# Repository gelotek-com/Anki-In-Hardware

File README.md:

# Physical Anki Device

Building a physical flashcard device inspired by **Anki** and **spaced repetition**.

## YouTube Series
Watch the full project here:  
🎥 https://www.youtube.com/playlist?list=PLZI8gkIZC2W3yhb4EUrMZ4vrkucjjzuon
## My website
My website for more details:
https://gelotek.com/AIH/

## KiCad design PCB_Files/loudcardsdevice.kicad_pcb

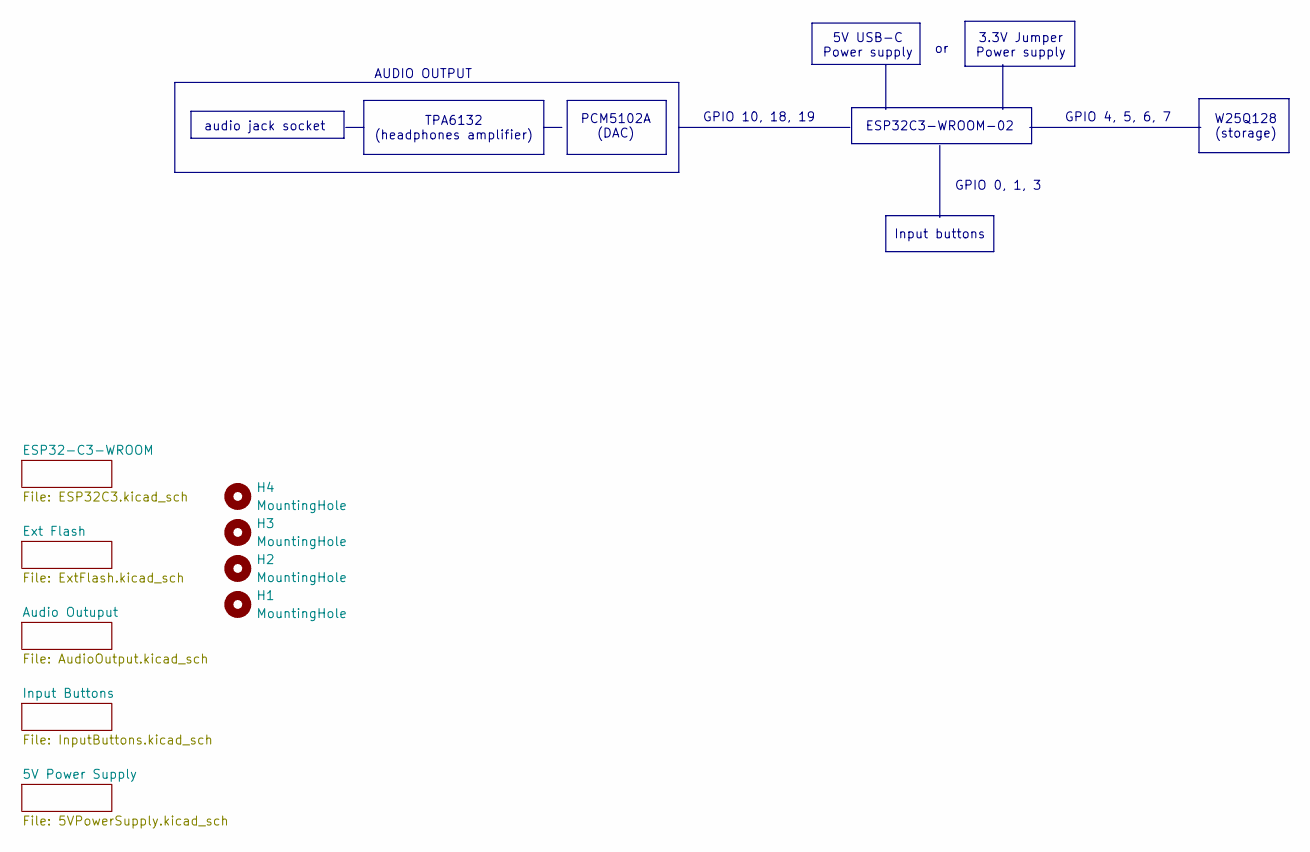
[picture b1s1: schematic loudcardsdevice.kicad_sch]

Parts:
H1, H2, H3, H4: MountingHole; MountingHole_2.1mm

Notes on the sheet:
ESP32C3-WROOM-02
GPIO 10, 18, 19
PCM5102A (DAC)
3.3V Jumper Power supply
GPIO 0, 1, 3
5V USB-C Power supply
AUDIO OUTPUT
TPA6132 (headphones amplifier)
Input buttons
W25Q128 (storage)
GPIO 4, 5, 6, 7
audio jack socket

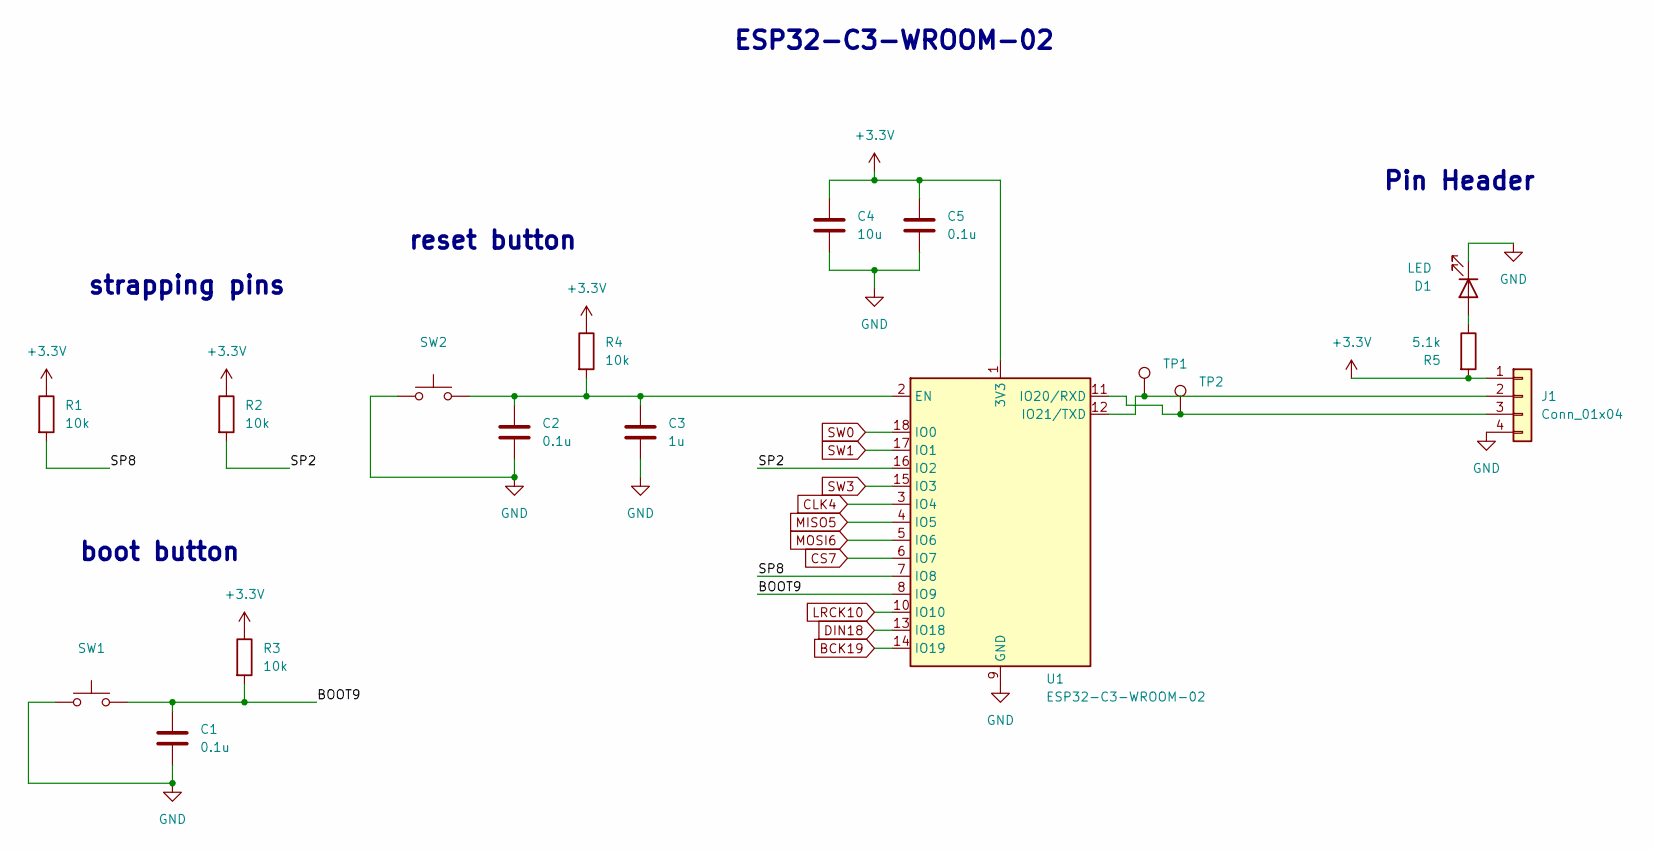
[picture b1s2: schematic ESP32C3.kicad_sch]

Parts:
C1, C2, C5: 0.1u; C_0603_1608Metric; MPN 0603B104K250CT
C3: 1u; C_0603_1608Metric; MPN CL10A105KO8NNNC
C4: 10u; C_0603_1608Metric; MPN CL10A106MQ8NNNC
D1: LED; LED_0603_1608Metric; MPN YLED0603R
J1: Conn_01x04; PinHeader_1x04_P2.54mm_Vertical; MPN PZ254V-11-04P
R1, R2, R3, R4: 10k; R_0603_1608Metric; MPN RC0603FR-0710KL
R5: 5.1k; R_0603_1608Metric; MPN FRC0603F5101TS
SW1, SW2: SW_Push; SW_PUSH_6mm; MPN TS665CJ
TP1, TP2: TestPoint; TestPoint_Pad_1.0x1.0mm
U1: ESP32-C3-WROOM-02; MPN ESP32-C3-WROOM-02-H4

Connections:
+3.3V: C4.1, C5.1, J1.1, R1.1, R2.1, R3.1, R4.1, R5.2, U1.1 (3V3); also elsewhere on the board
/ESP32-C3-WROOM/BOOT9: C1.1, R3.2, SW1.2, U1.8 (IO9)
/ESP32-C3-WROOM/SP2: R2.2, U1.16 (IO2)
/ESP32-C3-WROOM/SP8: R1.2, U1.7 (IO8)
BCK19: U1.14 (IO19); also elsewhere on the board
CLK4: U1.3 (IO4); also elsewhere on the board
CS7: U1.6 (IO7); also elsewhere on the board
DIN18: U1.13 (IO18); also elsewhere on the board
GND: C1.2, C2.2, C3.2, C4.2, C5.2, D1.1 (K), J1.4, SW1.1, SW2.1, U1.9 (GND), U1.19 (GND); also elsewhere on the board
LRCK10: U1.10 (IO10); also elsewhere on the board
MISO5: U1.4 (IO5); also elsewhere on the board
MOSI6: U1.5 (IO6); also elsewhere on the board
unnamed: D1.2 (A), R5.1
unnamed: J1.2, TP1.1, U1.12 (IO21/TXD)
unnamed: J1.3, TP2.1, U1.11 (IO20/RXD)
unnamed: C2.1, C3.1, R4.2, SW2.2, U1.2 (EN)
SW0: U1.18 (IO0); also elsewhere on the board
SW1: U1.17 (IO1); also elsewhere on the board
SW3: U1.15 (IO3); also elsewhere on the board

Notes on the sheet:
strapping pins
boot button
Pin Header
reset button
ESP32-C3-WROOM-02

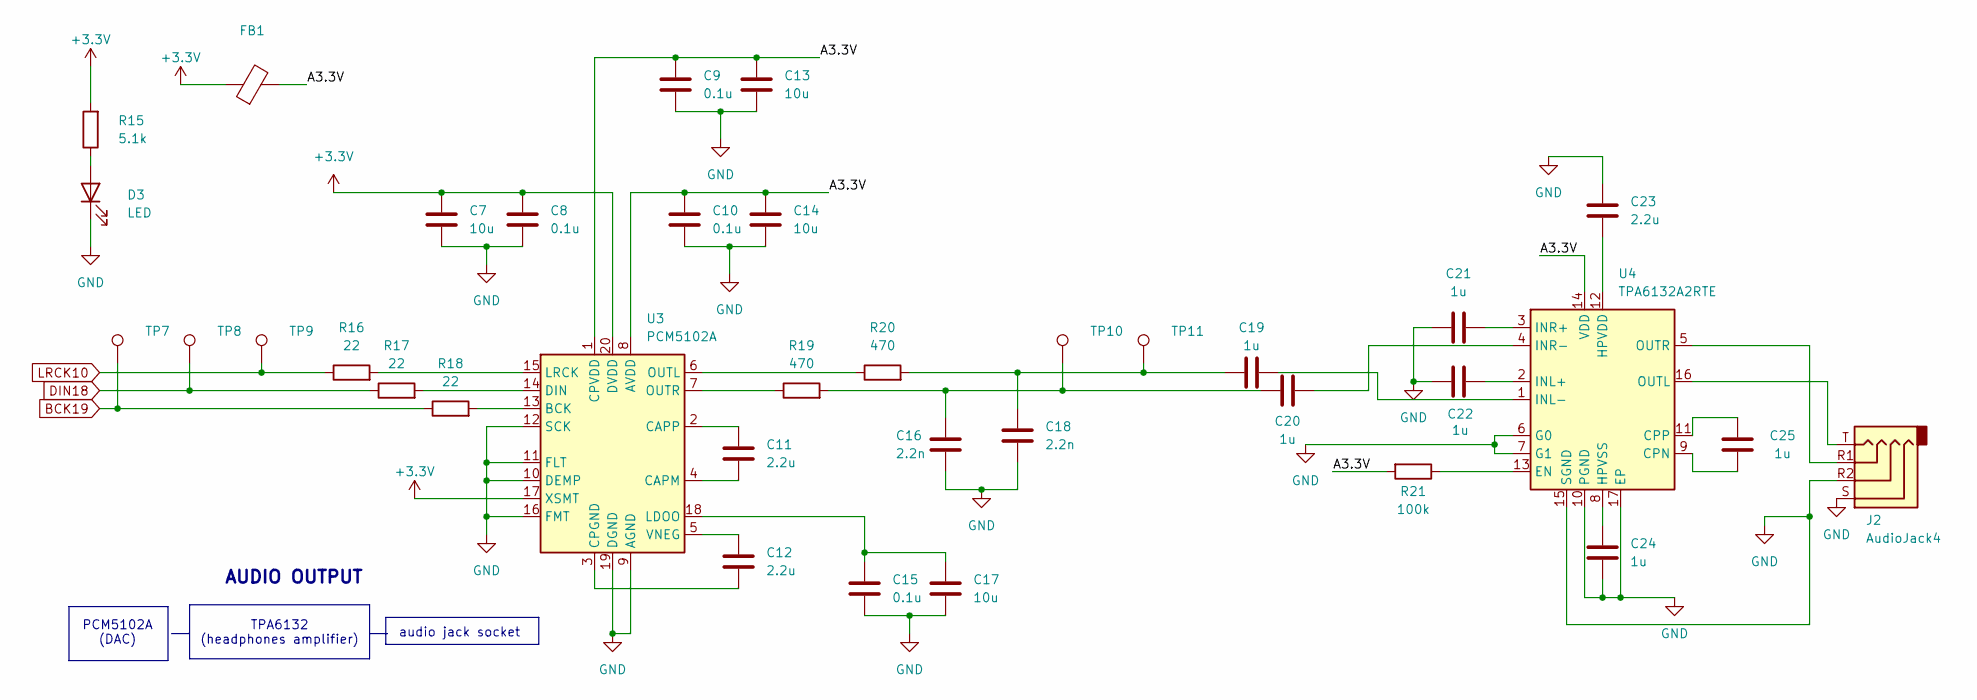
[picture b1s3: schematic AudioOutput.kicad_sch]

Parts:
C7, C13, C14, C17: 10u; C_0603_1608Metric; MPN CL10A106MQ8NNNC
C8, C9, C10, C15: 0.1u; C_0603_1608Metric; MPN 0603B104K250CT
C11, C12, C23: 2.2u; C_0603_1608Metric; MPN CL10A225KQ8NNNC
C16, C18: 2.2n; C_0603_1608Metric; MPN 0603B222K500CT
C19, C20, C21, C22, C24, C25: 1u; C_0603_1608Metric; MPN CL10A105KO8NNNC
D3: LED; LED_0603_1608Metric; MPN YLED0603R
FB1: 600Ω @ 100MHzSize 0805 preferred for audio rails.; L_0805_2012Metric; MPN BLM21PG221SN1D
J2: AudioJack4; Jack_3.5mm_PJ320D_Horizontal; MPN PJ-320D
R15: 5.1k; R_0603_1608Metric; MPN FRC0603F5101TS
R16, R17, R18: 22; R_0603_1608Metric; MPN RC0603FR-0722RL
R19, R20: 470; R_0603_1608Metric; MPN 0603WAF4700T5E
R21: 100k; R_0603_1608Metric; MPN RC0603FR-07100KL
TP7, TP8, TP9, TP10, TP11: TestPoint; TestPoint_Pad_1.0x1.0mm
U3: PCM5102A; TSSOP-20_4.4x6.5mm_P0.65mm; MPN PCM5102APWR
U4: TPA6132A2RTE; WQFN-16-1EP_3x3mm_P0.5mm_EP1.6x1.6mm_ThermalVias; MPN TPA6132A2RTER

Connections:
+3.3V: C7.1, C8.1, FB1.1, R15.2, U3.17 (XSMT), U3.20 (DVDD); also elsewhere on the board
/Audio Outuput/A3.3V: C9.1, C10.1, C13.1, C14.1, FB1.2, R21.2, U3.1 (CPVDD), U3.8 (AVDD), U4.14 (VDD)
BCK19: R18.1, TP7.1; also elsewhere on the board
DIN18: R17.1, TP8.1; also elsewhere on the board
GND: C7.2, C8.2, C9.2, C10.2, C13.2, C14.2, C15.2, C16.2, C17.2, C18.2, C21.1, C22.1, C23.2, C24.1, D3.1 (K), J2.R2, J2.S, U3.9 (AGND), U3.10 (DEMP), U3.11 (FLT), U3.12 (SCK), U3.16 (FMT), U3.19 (DGND), U4.6 (G0), U4.7 (G1), U4.10 (PGND), U4.15 (SGND), U4.17 (EP); also elsewhere on the board
LRCK10: R16.1, TP9.1; also elsewhere on the board
unnamed: C16.1, C20.1, R19.2, TP10.1
unnamed: C18.1, C19.1, R20.2, TP11.1
unnamed: D3.2 (A), R15.1
unnamed: R18.2, U3.13 (BCK)
unnamed: C11.2, U3.4 (CAPM)
unnamed: C11.1, U3.2 (CAPP)
unnamed: C12.2, U3.3 (CPGND)
unnamed: R17.2, U3.14 (DIN)
unnamed: C15.1, C17.1, U3.18 (LDOO)
unnamed: R16.2, U3.15 (LRCK)
unnamed: R20.1, U3.6 (OUTL)
unnamed: R19.1, U3.7 (OUTR)
unnamed: C12.1, U3.5 (VNEG)
unnamed: C25.2, U4.9 (CPN)
unnamed: C25.1, U4.11 (CPP)
unnamed: R21.1, U4.13 (EN)
unnamed: C23.1, U4.12 (HPVDD)
unnamed: C24.2, U4.8 (HPVSS)
unnamed: C22.2, U4.2 (INL+)
unnamed: C19.2, U4.1 (INL-)
unnamed: C21.2, U4.3 (INR+)
unnamed: C20.2, U4.4 (INR-)
unnamed: J2.T, U4.16 (OUTL)
unnamed: J2.R1, U4.5 (OUTR)

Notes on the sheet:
audio jack socket
PCM5102A (DAC)
TPA6132 (headphones amplifier)
AUDIO OUTPUT

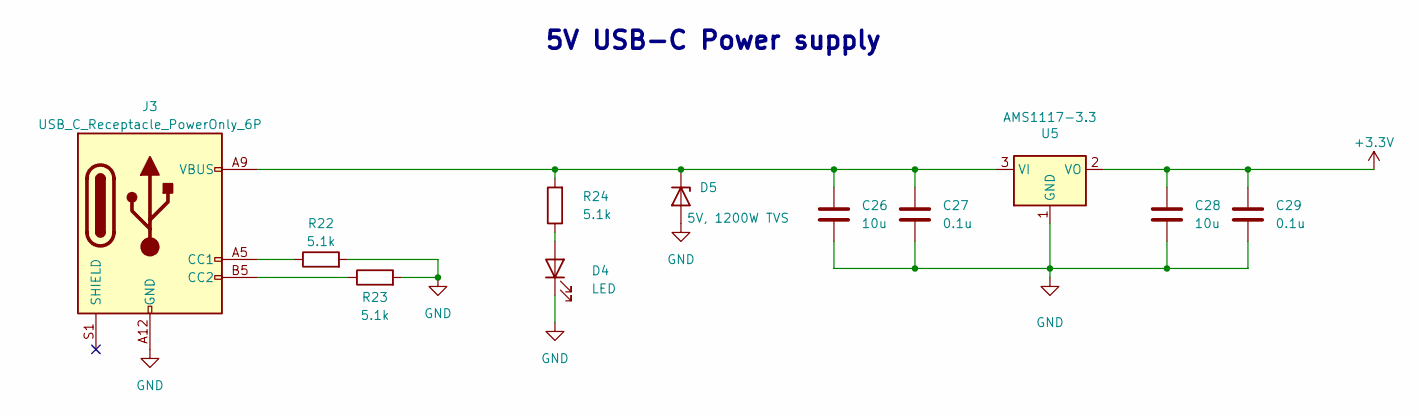
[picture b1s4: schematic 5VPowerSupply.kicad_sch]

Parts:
C26, C28: 10u; C_0603_1608Metric; MPN CL10A106MQ8NNNC
C27, C29: 0.1u; C_0603_1608Metric
D4: LED; LED_0603_1608Metric; MPN YLED0603R
D5: 5V, 1200W TVS; D_SOD-323F; MPN SD05.TCT
J3: USB_C_Receptacle_PowerOnly_6P; USB_C_Receptacle_GCT_USB4125-xx-x-0190_6P_TopMnt_Horizontal; MPN USB4125-GF-A-0190
R22, R23, R24: 5.1k; R_0603_1608Metric; MPN FRC0603F5101TS
U5: AMS1117-3.3; SOT-223-3_TabPin2; MPN AMS1117-3.3

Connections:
+3.3V: C28.1, C29.1, U5.2 (VO); also elsewhere on the board
GND: C26.2, C27.2, C28.2, C29.2, D4.1 (K), D5.2 (A), J3.A12 (GND), J3.B12 (GND), R22.2, R23.2, U5.1 (GND); also elsewhere on the board
unnamed: D4.2 (A), R24.1
unnamed: C26.1, C27.1, D5.1 (K), J3.A9 (VBUS), J3.B9 (VBUS), R24.2, U5.3 (VI)
unnamed: J3.A5 (CC1), R22.1
unnamed: J3.B5 (CC2), R23.1

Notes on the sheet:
5V USB-C Power supply

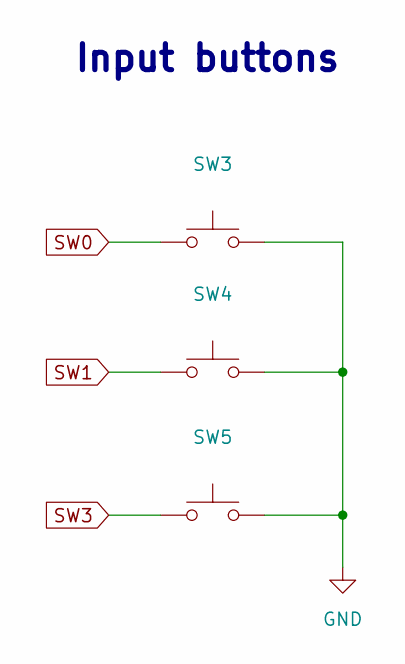
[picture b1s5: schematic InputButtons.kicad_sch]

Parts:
SW3, SW4, SW5: SW_Push; SW_PUSH_6mm; MPN TS665CJ

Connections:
GND: SW3.2, SW4.2, SW5.2; also elsewhere on the board
SW0: SW3.1; also elsewhere on the board
SW1: SW4.1; also elsewhere on the board
SW3: SW5.1; also elsewhere on the board

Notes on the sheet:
Input buttons

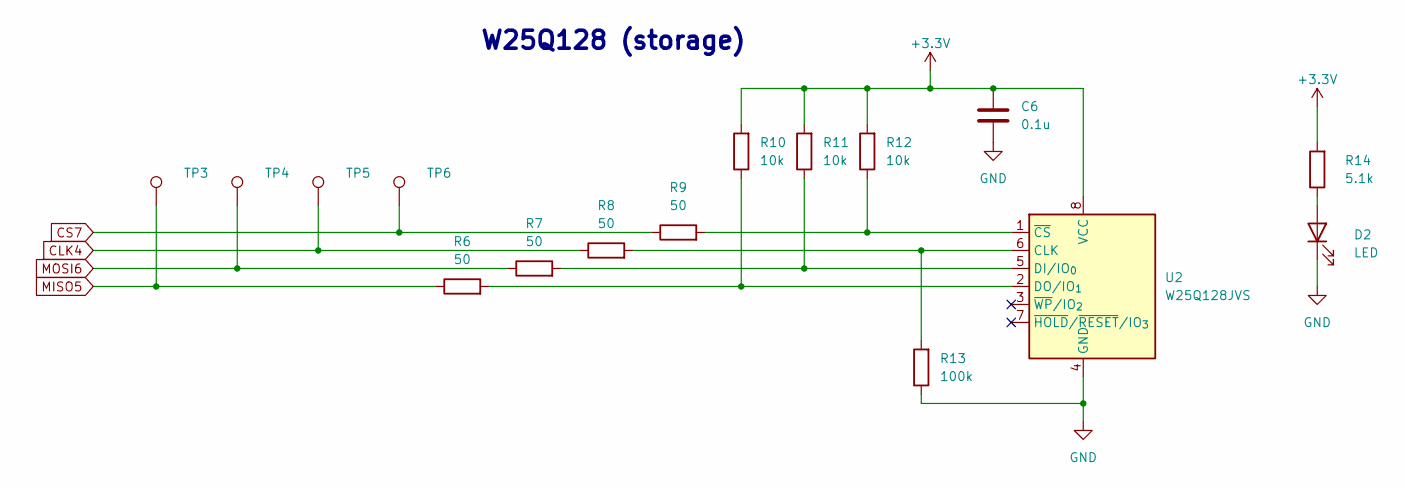
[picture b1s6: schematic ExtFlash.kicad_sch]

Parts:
C6: 0.1u; C_0603_1608Metric; MPN 0603B104K250CT
D2: LED; LED_0603_1608Metric; MPN YLED0603R
R6, R7, R8, R9: 50; R_0603_1608Metric; MPN RT0603BRE0750RL
R10, R11, R12: 10k; R_0603_1608Metric; MPN RC0603FR-0710KL
R13: 100k; R_0603_1608Metric; MPN RC0603FR-07100KL
R14: 5.1k; R_0603_1608Metric; MPN FRC0603F5101TS
TP3, TP4, TP5, TP6: TestPoint; TestPoint_Pad_1.0x1.0mm
U2: W25Q128JVS; SOIC-8_5.3x5.3mm_P1.27mm; MPN W25Q128JVSIQ

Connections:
+3.3V: C6.1, R10.2, R11.2, R12.2, R14.2, U2.8 (VCC); also elsewhere on the board
CLK4: R8.1, TP5.1; also elsewhere on the board
CS7: R9.1, TP6.1; also elsewhere on the board
GND: C6.2, D2.1 (K), R13.1, U2.4 (GND); also elsewhere on the board
MISO5: R6.1, TP3.1; also elsewhere on the board
MOSI6: R7.1, TP4.1; also elsewhere on the board
unnamed: D2.2 (A), R14.1
unnamed: R8.2, R13.2, U2.6 (CLK)
unnamed: R7.2, R11.1, U2.5 (DI/IO_{0})
unnamed: R6.2, R10.1, U2.2 (DO/IO_{1})
unnamed: R9.2, R12.1, U2.1 (~CS)

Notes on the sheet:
W25Q128 (storage)

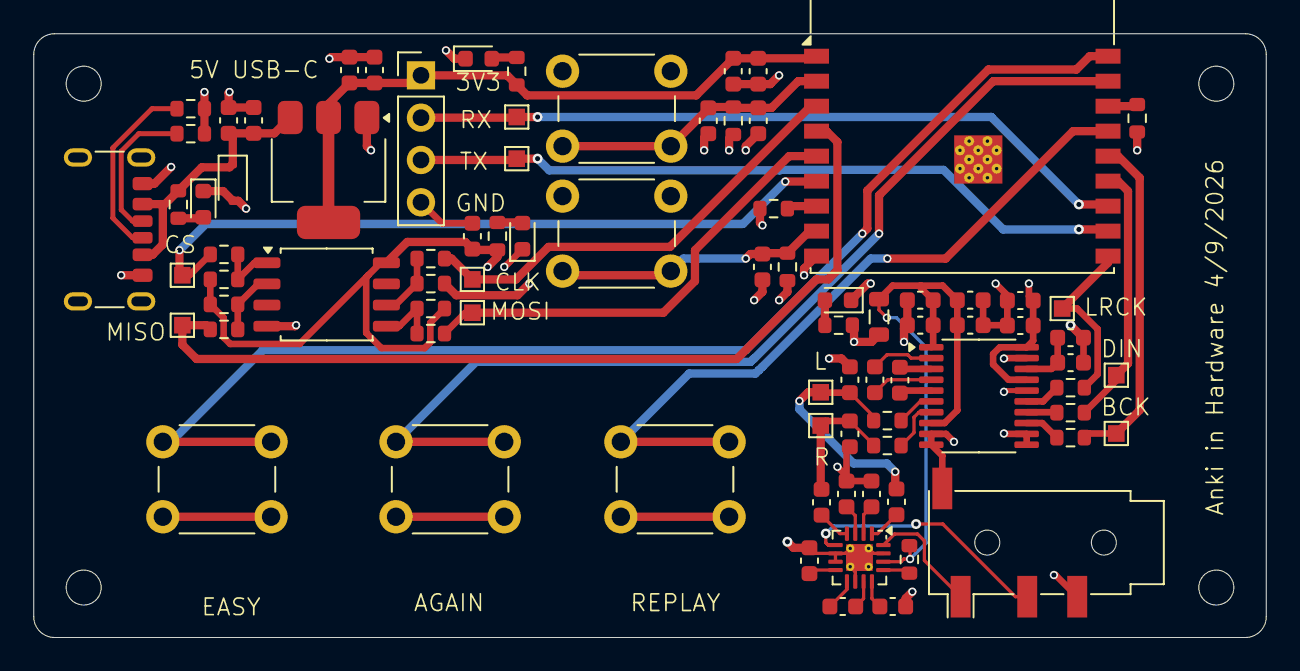
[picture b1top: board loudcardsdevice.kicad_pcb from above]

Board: 4 copper layers, 74.0 x 36.2 mm, 87 parts (0 on the bottom side), 53 nets.

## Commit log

2025-10-24 Add project description to README.md
2025-10-31 part 3
2025-11-07 part 4
2025-11-14 part5
2025-11-21 part 6
2025-11-28 part 7
2025-11-28 part 7 (adjusted platformio.ini)
2026-01-07 part8
2026-01-12 part 9, added the external flash
2026-02-04 Part 10
2026-05-23 PCB files
2026-05-23 Add website link to README
    Added a link to my website for more details.
